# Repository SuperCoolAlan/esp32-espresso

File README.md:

# ESP32 Espresso Machine Controller

An open-source PID temperature controller for espresso machines, featuring WiFi connectivity and precise temperature control.

## Project Structure

```
esp32-espresso/
├── pid-controller/     # PCB design (atopile)
│   ├── main.ato        # Main circuit definition
│   ├── components/     # Custom component definitions
│   └── build/          # Generated manufacturing files
└── pyproject.toml      # Python dependencies
```

## Hardware

The controller board is designed in [atopile](https://atopile.io) and manufactured via JLCPCB.

### Features

- **ESP32-S3** microcontroller with WiFi/BLE
- **On-board AC-DC converter** (100-240V AC → 5V DC) - direct mains power
- **USB Type-C** for programming/debugging (also provides backup power)
- **MAX31855** K-type thermocouple interface for precise temperature measurement
- **External SSR control** for heater switching (supports 25A panel-mount SSRs)
- **Pressure sensor input** with 5V→3.3V level shifting
- **Status LEDs** for system state indication

See [pid-controller/README.md](pid-controller/README.md) for detailed board documentation.

## Building the PCB

```bash
# Install dependencies
uv sync

# Build the PCB
cd pid-controller
ato build
```

Manufacturing files will be generated in `pid-controller/build/default/`.

## License

See individual component licenses in their respective directories.

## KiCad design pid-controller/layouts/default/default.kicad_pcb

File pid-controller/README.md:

# ESP32-S3 PID Controller for Espresso Machine

A PID temperature controller board designed for the Rancilio Silvia espresso machine, built with [atopile](https://atopile.io).

## TODO

- [ ] **Fuse on AC input** - protects against shorts/overcurrent
- [ ] **MOV/TVS on AC input** - surge protection from mains spikes
- [ ] **TVS diodes on USB D+/D-** - ESD protection (e.g., USBLC6-2)
- [ ] **TVS on thermocouple inputs** - TC wires run outside enclosure
- [ ] **Power LED** - indicates board is powered
- [ ] **Reset button** - useful for development
- [ ] **Mounting holes** - for securing PCB in enclosure
- [ ] **Test points** - on key signals for debugging
- [ ] **Fiducials** - alignment markers for pick and place assembly

## Board Overview

This board provides closed-loop temperature control for an espresso machine boiler using a K-type thermocouple and an external solid-state relay.

### Major Components

| Component | Part Number | Description |
|-----------|-------------|-------------|
| MCU | ESP32-S3-WROOM-1-N8 | WiFi/BLE module, 8MB flash |
| AC-DC Converter | HLK-PM01 | 100-240V AC → 5V DC @ 600mA (3W) |
| Thermocouple IC | MAX31855KASA | K-type thermocouple-to-digital converter |
| Voltage Regulator | AMS1117-3.3 | 3.3V LDO (from 5V) |
| SSR Driver | BC817-40 | NPN transistor for external SSR control |
| Power Diode | SS14 | Schottky diode for USB/AC power OR-ing |

### Connectors / Terminals

| Connector | Pins | Function |
|-----------|------|----------|
| J_AC | 2 | AC mains input (Line, Neutral) |
| J_USB | USB-C | Programming/debugging + backup 5V power |
| J_TC | 2 | K-type thermocouple input (TC+, TC-) |
| J_SSR | 2 | External SSR control output (SSR+, SSR-) |
| J_PRESSURE | 3 | Pressure sensor input (+5V, Signal, GND) |

### Status LEDs

| LED | Color | Function |
|-----|-------|----------|
| LED_OK | Green | System running / OK |
| LED_HEAT | Orange | Heating element active |
| LED_ERR | Red | Error condition |

All LEDs are active-low (accent driven by GPIO sinking current).

## Pin Assignments

### ESP32-S3 GPIO Usage

| GPIO | Function |
|------|----------|
| IO1 | Pressure sensor ADC input |
| IO4 | SSR control output |
| IO5 | Green LED (OK) |
| IO6 | Orange LED (Heating) |
| IO7 | Red LED (Error) |
| IO10 | SPI CS (MAX31855) |
| IO11 | SPI MOSI (unused) |
| IO12 | SPI CLK (MAX31855) |
| IO13 | SPI MISO (MAX31855) |
| IO19 | USB D- |
| IO20 | USB D+ |

## External SSR Wiring

This board outputs a control signal for an external panel-mount SSR (e.g., Fotek SSR-25DA or similar 25A SSR). The external SSR provides better heat dissipation for high-power loads.

```
Board J_SSR          External SSR (25A)         Heater
┌─────────┐          ┌─────────────┐           ┌──────┐
│ Pin 1 ──┼──────────┤ Input +     │           │      │
│ (SSR+)  │          │ (3-32VDC)   │           │      │
│         │          │             ├───────────┤ Load │
│ Pin 2 ──┼──────────┤ Input -     │    AC     │      │
│ (SSR-)  │          │             ├───────────┤      │
└─────────┘          └─────────────┘           └──────┘
```

## Circuit Features

- **AC-DC Power**: On-board HLK-PM01 isolated converter (100-240V AC → 5V DC)
- **USB Type-C**: For programming/debugging, with Schottky diode power OR-ing
- **Dual Power Sources**: USB power works when AC is disconnected (for bench programming)
- **Boot Circuit**: 10k pullup + 1µF RC delay on EN pin for reliable power-on reset
- **Boot Mode**: 10k pullup on GPIO0 for normal SPI flash boot
- **Decoupling**: 100nF + 10µF on 3.3V rail, 10µF + 22µF on LDO
- **Pressure Sensor**: 10k/20k voltage divider (5V → 3.3V) with 100nF filter cap

## Building

Requires [atopile](https://atopile.io) v0.12.4 or later.

```bash
cd pid-controller
ato build
```

Build outputs are placed in `build/default/`.

## BOM / Ordering

All components are available from JLCPCB/LCSC. Run `ato build` to generate the BOM and manufacturing files.

## License

See [LICENSE.txt](LICENSE.txt)

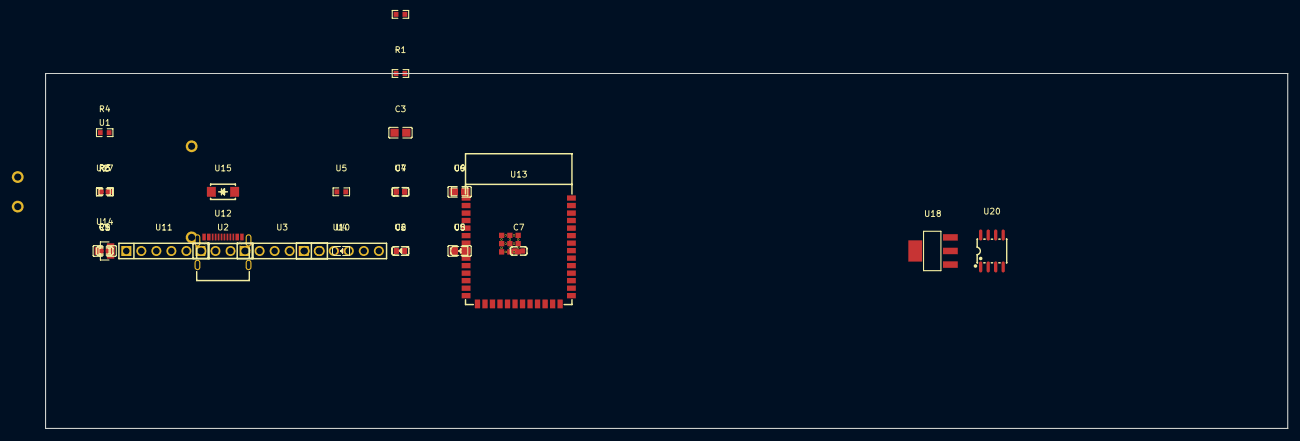
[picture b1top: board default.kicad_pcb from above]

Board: 2 copper layers, 210.0 x 60.0 mm, 32 parts (0 on the bottom side), 28 nets, no tracks yet.

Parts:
C1, C4, C7: 100nF ±10% 50V X7R; C0603
C2: 1µF ±10% 50V X5R; C0603
C3, C5: 10µF ±10% 25V X5R; C0805
C6: 22µF ±20% 25V X5R; C0805
C8: 100µF ±20% 6.3V X5R; C0805
R1, R2, R4: 10kΩ ±1% 100mW; R0603
R3: 20kΩ ±1% 100mW; R0603
R5, R6: 5.1kΩ ±1% 62.5mW; R0402
U1: PWRM-TH_HLK-PM01
U2: HDR-TH_4P-P2.54-V-M
U3, U10, U11: HDR-TH_6P-P2.54-V-M
U4, U8: LED0603-RD
U5: 150Ω ±1% 100mW; R0603
U6: LED0603-FD_BLUE
U7: 120Ω ±1% 100mW; R0603
U9: 100Ω ±1% 100mW; R0603
U12: USB-C-SMD_TYPE-C16PIN
U13: WIFIM-SMD_ESP32-S3-WROOM-1-N8
U14: SOT-23-3_L2.9-W1.3-P1.90-LS2.4-BR
U15: SMA_L4.2-W2.6-LS5.0-RD_1
U17: 1kΩ ±1% 100mW; R0603
U18: SOT-223-3_L6.5-W3.4-P2.30-LS7.0-BR
U20: SO-8_L4.9-W3.9-P1.27-LS5.9-BL

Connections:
A5: R5.1, U12.A5
B5: R6.1, U12.B5
GND: C1.2, C2.2, C3.2, C4.2, C5.2, C6.2, C7.2, C8.2, R3.2, R5.2, R6.2, U1.3, U2.3, U12.1, U12.2, U12.3, U12.4, U12.A1B12, U12.B1A12, U13.1, U13.40, U13.41, U14.2, U18.1, U20.1
ac_line: U1.1, U11.1
ac_neutral: U1.2, U11.2
base: U14.1, U17.2
conn-anode: U12.A4B9, U12.B4A9, U15.1
cs: U13.18, U20.6
en: C2.1, R2.2, U13.3
footprint-anode-0: U4.2, U5.2
footprint-anode-1: U6.2, U7.2
footprint-anode-2: U8.2, U9.2
footprint-ctrl-0: U4.1, U13.7
footprint-ctrl-1: U6.1, U13.6
footprint-ctrl-2: U8.1, U13.5
footprint-ctrl-3: U13.4, U17.1
io0: R1.2, U13.27
output: R4.1, U2.2
power-VCC: C3.1, C4.1, C6.1, C7.1, R1.1, R2.1, U5.1, U7.1, U9.1, U13.2, U18.2, U20.4
power_5v-VCC: C5.1, C8.1, U1.4, U2.1, U3.1, U15.2, U18.3
pressure_adc: C1.1, R3.1, R4.2, U13.26
sck: U13.20, U20.5
spi_miso: U13.21, U20.7
ssr_neg: U3.2, U14.3
tc_minus: U10.2, U20.2
tc_plus: U10.1, U20.3
usb_dm: U12.A7, U12.B7, U13.13
usb_dp: U12.A6, U12.B6, U13.14
